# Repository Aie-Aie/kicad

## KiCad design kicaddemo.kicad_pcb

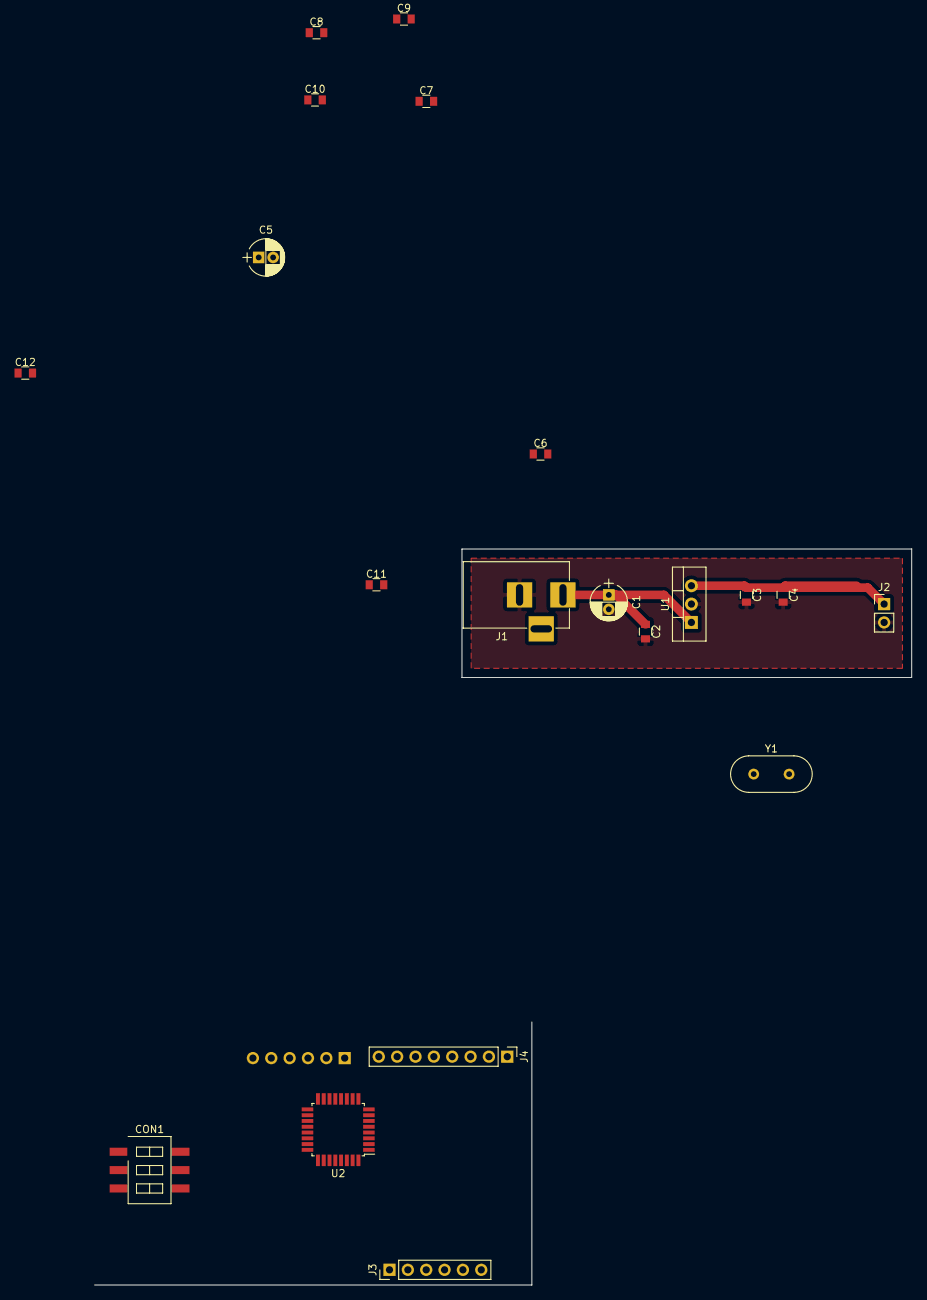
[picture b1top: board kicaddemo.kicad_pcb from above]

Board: 2 copper layers, 21 parts (1 on the bottom side), 26 nets.

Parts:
C1: 0.1uF; CP_Radial_D5.0mm_P2.00mm
C2, C6: 18pF; C_0805
C3, C8, C11: .01uF; C_0805
C4, C9, C12: 0.1uF; C_0805
C5: 100uF, 25V; CP_Radial_D5.0mm_P2.00mm
C7, C10: 10uF; C_0805
CON1: AVR-ISP-6; SW_DIP_x3_W8.61mm_Slide_LowProfile
J1: Barrel_Jack; BARREL_JACK
J2: Conn_01x02; Pin_Header_Straight_1x02_Pitch2.54mm
J3, J5: Conn_01x06_Female; Socket_Strip_Straight_1x06_Pitch2.54mm
J4: Conn_01x08_Female; Socket_Strip_Straight_1x08_Pitch2.54mm
U1: L7805; TO-220-3_Vertical
U2: ATMEGA328PB-AU; TQFP-32_7x7mm_Pitch0.8mm
Y1: Crystal; Crystal_HC18-U_Vertical

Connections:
+5V: C1.1, C3.1, C4.1, C8.1, C9.1, C10.1, C11.1, C12.1, CON1.2, J2.1, U1.3, U2.4, U2.18
/A0: J3.1, U2.23
/A1: J3.2, U2.24
/A2: J3.3, U2.25
/A3: J3.4, U2.26
/A4: J3.5, U2.27
/A5: J3.6, U2.28
/A6: CON1.5, U2.29
/D0: J4.1, U2.30
/D1: J4.2, U2.31
/D2: J4.3, U2.32
/D3: J4.4, U2.1
/D4: J4.5, U2.2
/D5: J4.6, U2.9
/D6: J4.7, U2.10
/D7: J4.8, U2.11
/D8: J5.1, U2.12
/D9: J5.2, U2.13
/D10: J5.3, U2.14
/MISO: CON1.1, J5.5, U2.16
/MOSI: CON1.4, J5.4, U2.15
/SCK: CON1.3, J5.6, U2.17
GND: C1.2, C2.2, C3.2, C4.2, C5.2, C6.2, C7.2, C8.2, C9.2, C10.2, C11.2, C12.2, CON1.6, J1.2, J2.2, U1.2, U2.5, U2.21
unnamed: C2.1, Y1.1
unnamed: C5.1, C7.1, J1.1, U1.1
unnamed: C6.1, Y1.2

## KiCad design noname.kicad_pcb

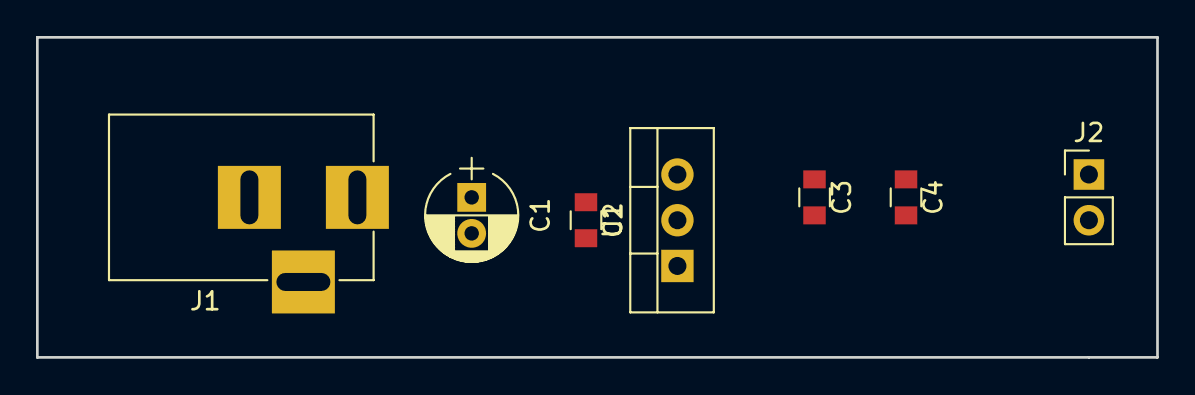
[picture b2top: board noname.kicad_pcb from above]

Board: 2 copper layers, 62.2 x 17.8 mm, 7 parts (0 on the bottom side), 3 nets, no tracks yet.

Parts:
C1: 100uF, 25V; CP_Radial_D5.0mm_P2.00mm
C2, C3: 10uF; C_0805
C4: 0.1uF; C_0805
J1: Barrel_Jack; BARREL_JACK
J2: Conn_01x02; Pin_Header_Straight_1x02_Pitch2.54mm
U1: L7805; TO-220-3_Vertical

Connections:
+5V: C3.1, C4.1, J2.1, U1.3
GND: C1.2, C3.2, C4.2, J1.2, J2.2, U1.2
unnamed: C1.1, J1.1, U1.1

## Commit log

2018-04-06 added
